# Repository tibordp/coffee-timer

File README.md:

# Coffee Timer

Simple kitchen timer using ATTiny85, a pair of 74HC595 shift registers and a 7-segment LED display.

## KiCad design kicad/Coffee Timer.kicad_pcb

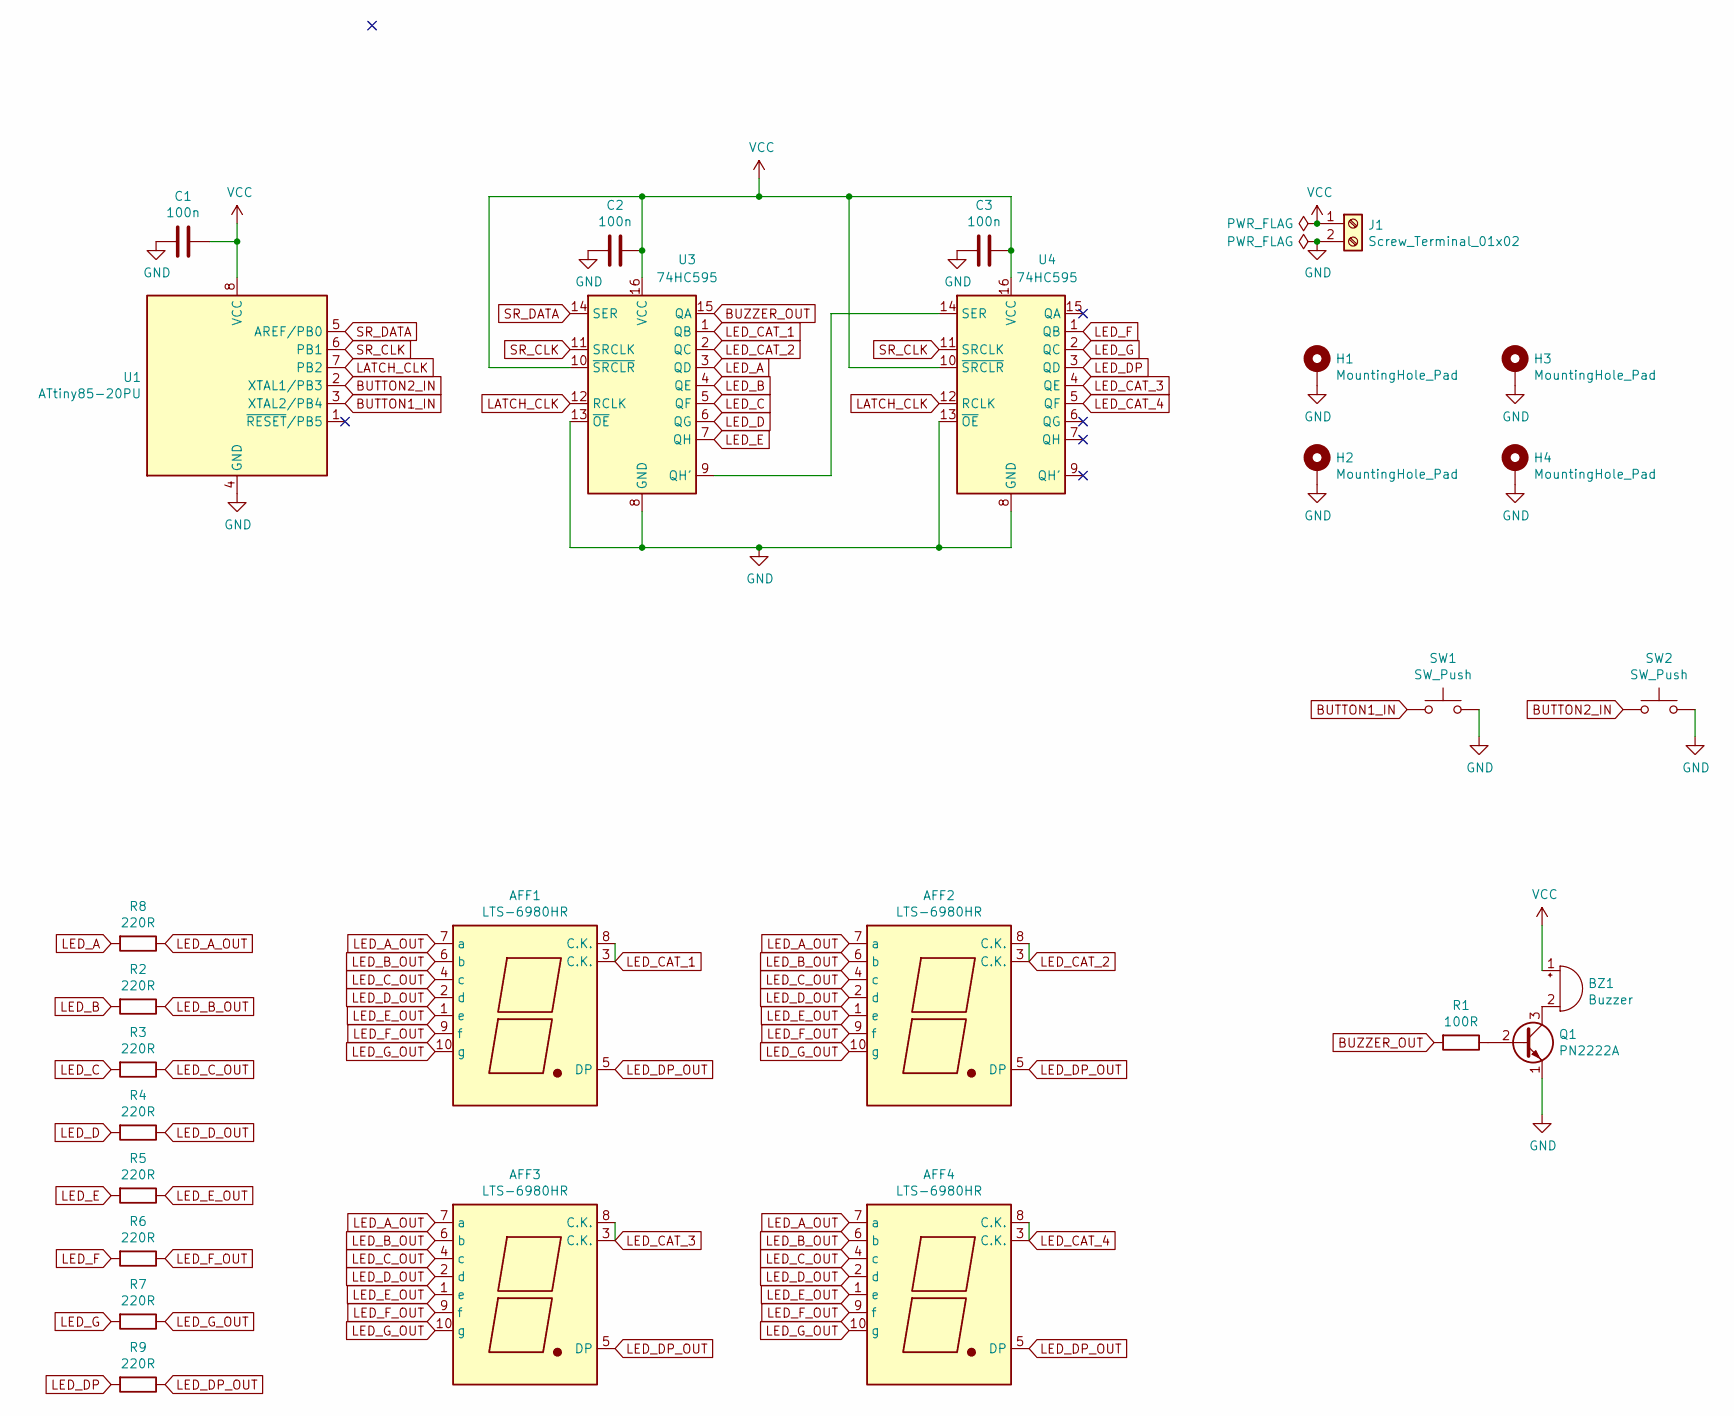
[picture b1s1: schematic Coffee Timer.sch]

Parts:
AFF1, AFF2, AFF3, AFF4: LTS-6980HR; 7SegmentLED_LTS6760_LTS6780
BZ1: Buzzer; Buzzer_12x9.5RM7.6
C1, C2, C3: 100n; C_Disc_D5.0mm_W2.5mm_P5.00mm
H1, H2, H3, H4: MountingHole_Pad; MountingHole_2.5mm_Pad_TopBottom
J1: Screw_Terminal_01x02; TerminalBlock_TE_282834-2_1x02_P2.54mm_Horizontal
Q1: PN2222A; TO-92_Inline_Wide
R1: 100R; R_Axial_DIN0204_L3.6mm_D1.6mm_P7.62mm_Horizontal
R2, R3, R4, R5, R6, R7, R8, R9: 220R; R_Axial_DIN0204_L3.6mm_D1.6mm_P7.62mm_Horizontal
SW1, SW2: SW_Push; SW_PUSH_6mm
U1: ATtiny85-20PU; DIP-8_W7.62mm
U3, U4: 74HC595; DIP-16_W7.62mm

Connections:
BUTTON1_IN: SW1.1, U1.3 (XTAL2/PB4)
BUTTON2_IN: SW2.1, U1.2 (XTAL1/PB3)
BUZZER_OUT: R1.2, U3.15 (QA)
GND: C1.2, C2.2, C3.2, H1.1, H2.1, H3.1, H4.1, J1.2, Q1.1 (E), SW1.2, SW2.2, U1.4 (GND), U3.8 (GND), U3.13 (~OE), U4.8 (GND), U4.13 (~OE)
LATCH_CLK: U1.7 (PB2), U3.12 (RCLK), U4.12 (RCLK)
LED_A: R8.2, U3.3 (QD)
LED_A_OUT: AFF1.7 (a), AFF2.7 (a), AFF3.7 (a), AFF4.7 (a), R8.1
LED_B: R2.2, U3.4 (QE)
LED_B_OUT: AFF1.6 (b), AFF2.6 (b), AFF3.6 (b), AFF4.6 (b), R2.1
LED_C: R3.2, U3.5 (QF)
LED_CAT_1: AFF1.3 (C.K.), AFF1.8 (C.K.), U3.1 (QB)
LED_CAT_2: AFF2.3 (C.K.), AFF2.8 (C.K.), U3.2 (QC)
LED_CAT_3: AFF3.3 (C.K.), AFF3.8 (C.K.), U4.4 (QE)
LED_CAT_4: AFF4.3 (C.K.), AFF4.8 (C.K.), U4.5 (QF)
LED_C_OUT: AFF1.4 (c), AFF2.4 (c), AFF3.4 (c), AFF4.4 (c), R3.1
LED_D: R4.2, U3.6 (QG)
LED_DP: R9.2, U4.3 (QD)
LED_DP_OUT: AFF1.5 (DP), AFF2.5 (DP), AFF3.5 (DP), AFF4.5 (DP), R9.1
LED_D_OUT: AFF1.2 (d), AFF2.2 (d), AFF3.2 (d), AFF4.2 (d), R4.1
LED_E: R5.2, U3.7 (QH)
LED_E_OUT: AFF1.1 (e), AFF2.1 (e), AFF3.1 (e), AFF4.1 (e), R5.1
LED_F: R6.2, U4.1 (QB)
LED_F_OUT: AFF1.9 (f), AFF2.9 (f), AFF3.9 (f), AFF4.9 (f), R6.1
LED_G: R7.2, U4.2 (QC)
LED_G_OUT: AFF1.10 (g), AFF2.10 (g), AFF3.10 (g), AFF4.10 (g), R7.1
unnamed: BZ1.2 (+), Q1.3 (C)
unnamed: Q1.2 (B), R1.1
unnamed: U3.9 (QH'), U4.14 (SER)
SR_CLK: U1.6 (PB1), U3.11 (SRCLK), U4.11 (SRCLK)
SR_DATA: U1.5 (AREF/PB0), U3.14 (SER)
VCC: BZ1.1 (-), C1.1, C2.1, C3.1, J1.1, U1.8 (VCC), U3.10 (~SRCLR), U3.16 (VCC), U4.10 (~SRCLR), U4.16 (VCC)

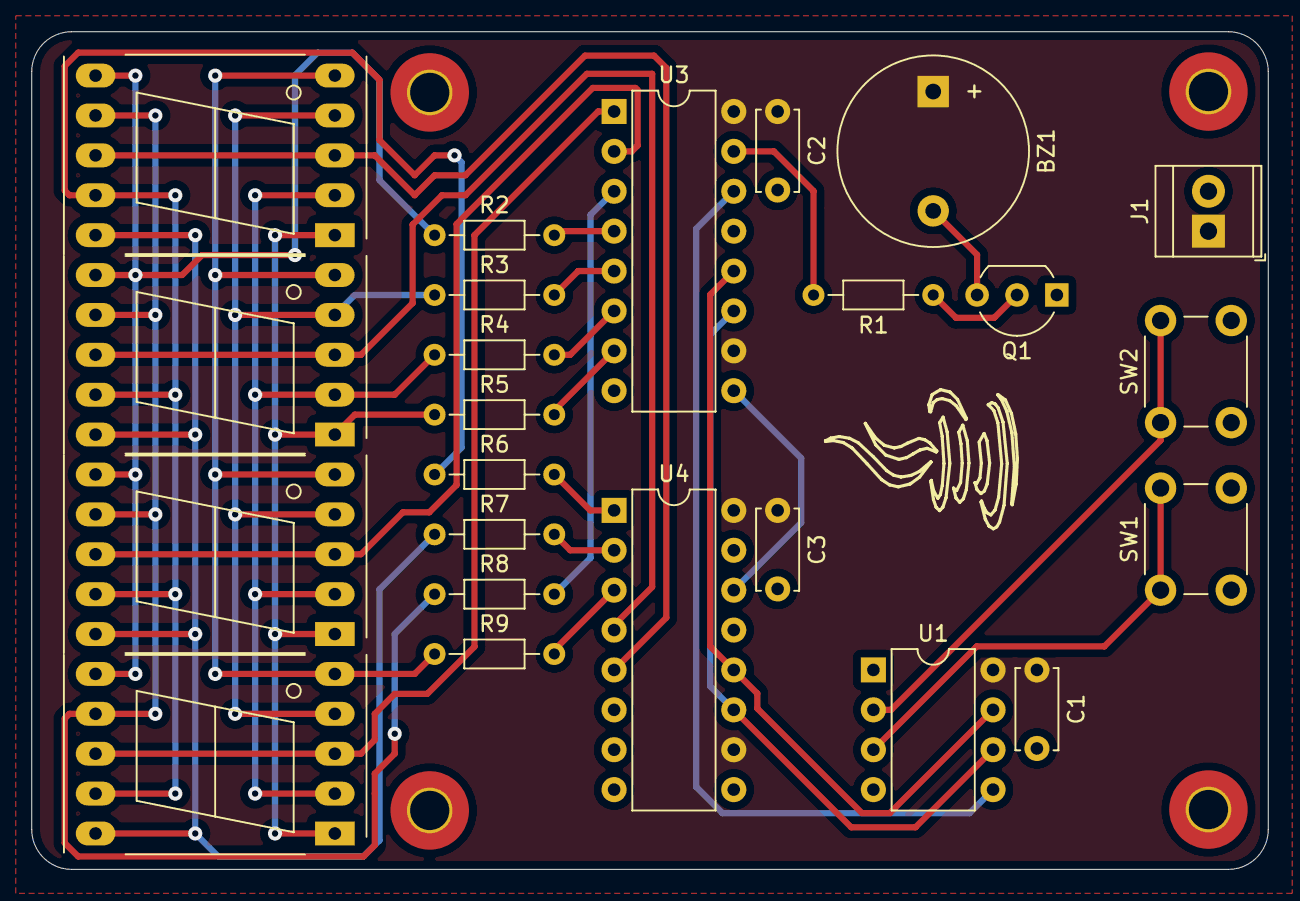
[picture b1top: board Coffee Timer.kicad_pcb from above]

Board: 2 copper layers, 78.7 x 53.3 mm, 28 parts (0 on the bottom side), 31 nets.

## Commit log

2021-01-07 Initial commit.
2021-01-07 ci: Add CI
2021-01-07 ci: Add CI (#1)
2021-01-13 feat: Update firmware code to match the hardware
2021-01-13 feat: Update firmware code to match the hardware (#2)
    * feat: Update firmware code to match the hardware
    * fix
    * fix
    * fix
    * fix
    * fix
2021-05-08 Change buzzing pattern a bit
2022-06-11 Add field callibration functionality
